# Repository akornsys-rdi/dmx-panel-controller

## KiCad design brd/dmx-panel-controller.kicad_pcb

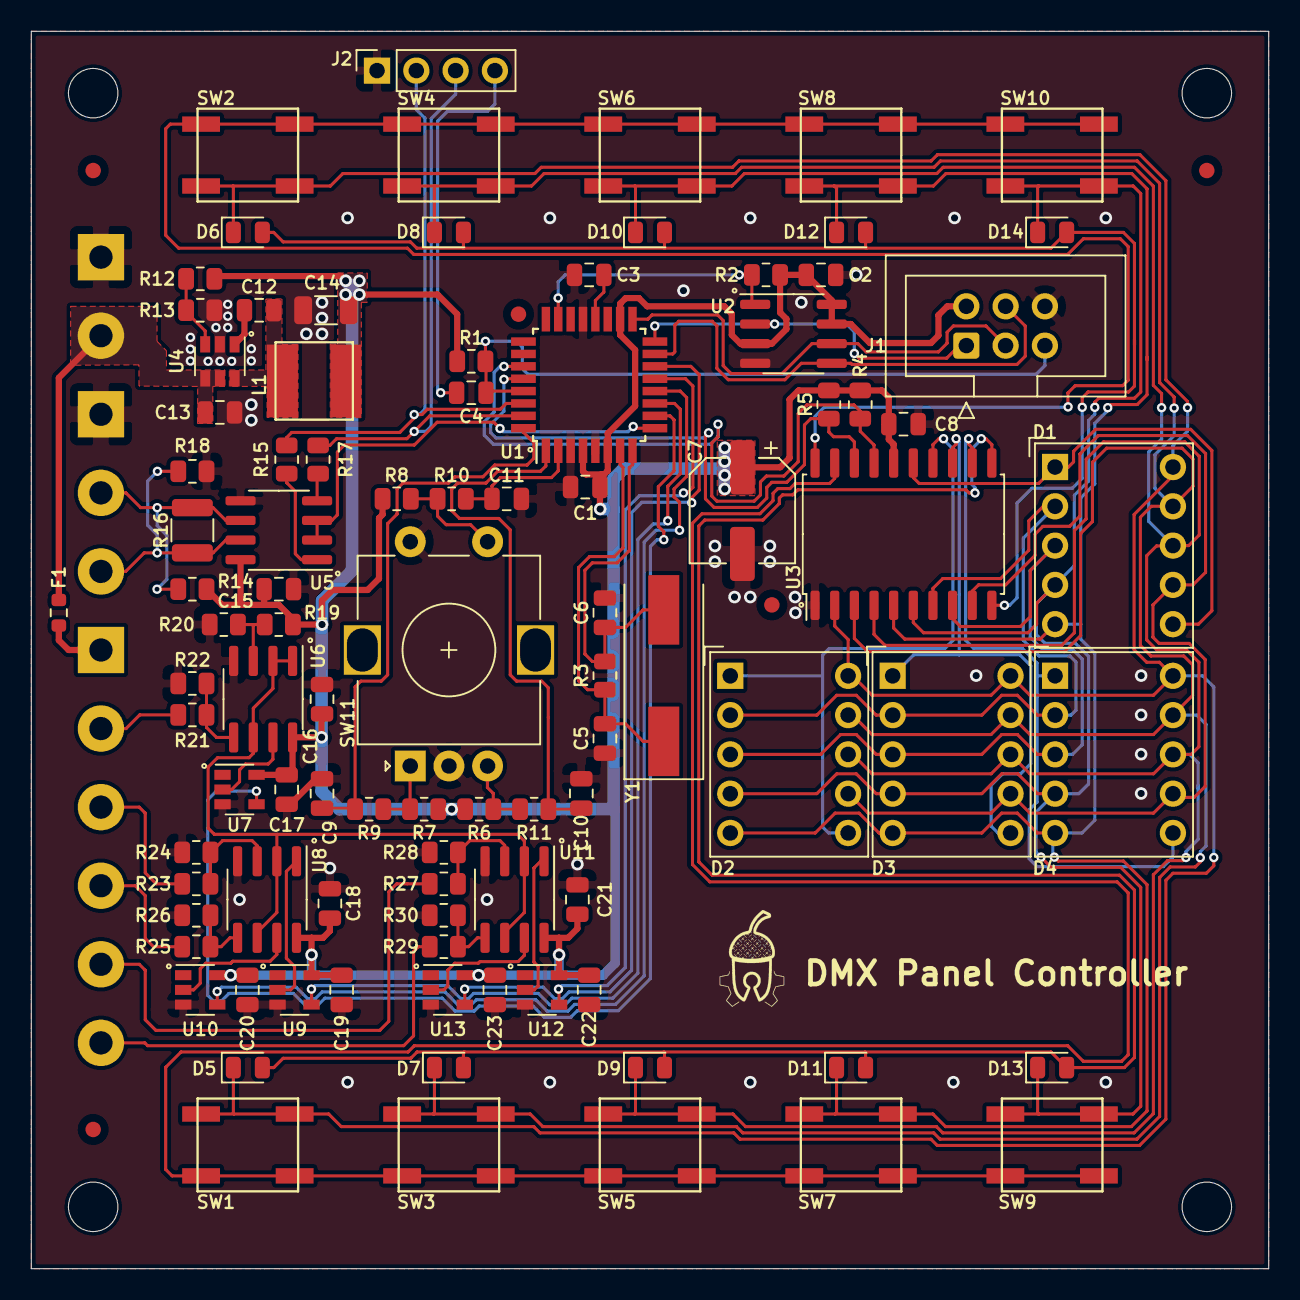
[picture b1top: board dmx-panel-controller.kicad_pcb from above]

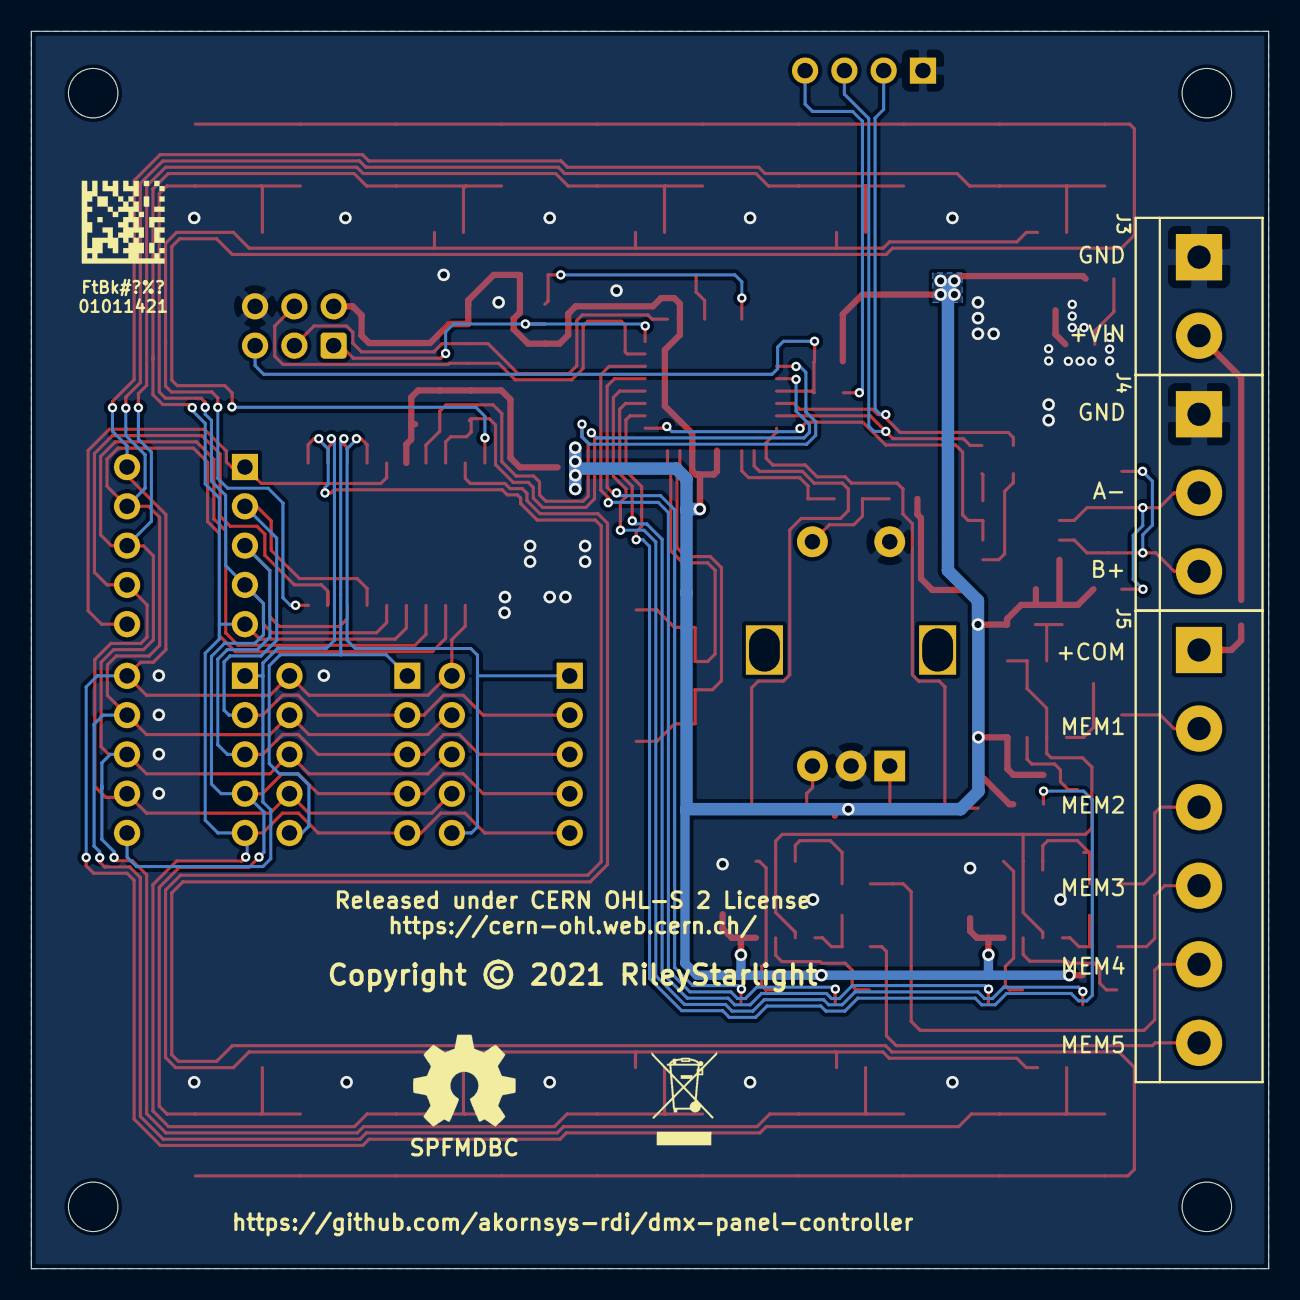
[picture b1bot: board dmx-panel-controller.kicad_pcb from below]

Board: 2 copper layers, 80.0 x 80.0 mm, 99 parts (3 on the bottom side), 69 nets.

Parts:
C1, C2, C3, C4, C8, C12, C15, C16, C17, C18, C19, C20, C21, C22, C23: 100nF; C_0805_2012Metric
C5, C6: 22pF; C_0805_2012Metric
C7: 220µF; CP_Elec_6.3x5.4
C9, C10, C11: 10nF; C_0805_2012Metric
C13: 4.7µF; C_0805_2012Metric
C14: 15µF; C_1206_3216Metric
D1, D2, D3, D4: SA39-12EWA; Sx39-1xxxxx
D5: RED; LED_0805_2012Metric
D6, D8, D10, D12, D13, D14: YELLOW; LED_0805_2012Metric
D7: GREEN; LED_0805_2012Metric
D9: BLUE; LED_0805_2012Metric
D11: WHITE; LED_0805_2012Metric
F1: 20mA; R_0603_1608Metric
J1: ISP; IDC-Header_2x03_P2.54mm_Vertical
J2: DEBUG; PinSocket_1x04_P2.54mm_Vertical
J3: POWER; TB006-508-02xx
J4: DMX; TB006-508-03xx
J5: INPUT; TB006-508-06xx
L1: 18µH; SRN5020
R1, R2, R4, R5, R6, R7, R8, R9, R10, R11, R19, R22, R24, R26, R28, R30: 10k; R_0805_2012Metric
R3: 1M; R_0805_2012Metric
R12: 88k7; R_0805_2012Metric
R13: 22k1; R_0805_2012Metric
R14, R18: 560R; R_0805_2012Metric
R15, R17: 1k; R_0805_2012Metric
R16: 120R; R_1210_3225Metric
R20: 4k7; R_0805_2012Metric
R21, R23, R25, R27, R29: 47k; R_0805_2012Metric
SW1, SW2, SW3, SW4, SW5, SW6, SW7, SW8, SW9, SW10: SW_Push; EVQ-Q2x0xW
SW11: Encoder; RotaryEncoder_Alps_EC11E-Switch_Vertical_H20mm
U1: ATmega328P-AU; TQFP-32_7x7mm_P0.8mm
U2: 25640; SOIC-8_3.9x4.9mm_P1.27mm
U3: TM1637; SOP-20_7.5x12.8mm_P1.27mm
U4: TPS560430; SOT-23-6
U5: SN65HVD82; SOIC-8_3.9x4.9mm_P1.27mm
U6, U8, U11: LM358; SOIC-8_3.9x4.9mm_P1.27mm
U7, U9, U10, U12, U13: 74LVC1G17; SOT-23-5
Y1: 16MHz; Crystal_SMD_HC49-SD

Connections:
+5V: C1.1, C2.1, C7.1, C8.1, C14.1, C15.1, C16.1, C17.1, C18.1, C19.1, C20.1, C21.1, C22.1, C23.1, J1.2, L1.2, R1.1, R2.1, R4.1, R5.1, R6.1, R7.1, R8.1, R12.1, R14.1, R19.1, U1.4, U1.6, U1.18, U2.3, U2.7, U2.8, U3.16, U5.8, U6.8, U7.5, U8.8, U9.5, U10.5, U11.8, U12.5, U13.5
+12V: C13.1, F1.1, J3.2, U4.4, U4.5
/DIR: U1.9, U5.2, U5.3
/ENC_A: C9.1, R9.2, U1.32
/ENC_B: C10.1, R11.2, U1.1
/HID/COL1: D1.1, D1.6, U3.15
/HID/COL2: D2.1, D2.6, U3.14
/HID/COL3: D3.1, D3.6, U3.13
/HID/COL4: D4.1, D4.6, U3.12
/HID/COL5: D5.2, D7.2, D9.2, D11.2, D13.2, U3.11
/HID/COL6: D6.2, D8.2, D10.2, D12.2, D14.2, U3.10
/HID/KEY1: SW1.1, SW3.1, SW5.1, SW7.1, SW9.1, U3.19
/HID/KEY2: SW2.1, SW4.1, SW6.1, SW8.1, SW10.1, U3.20
/HID/SEG_A: D1.10, D2.10, D3.10, D4.10, D5.1, D6.1, SW1.2, SW2.2, U3.2
/HID/SEG_B: D1.9, D2.9, D3.9, D4.9, D7.1, D8.1, SW3.2, SW4.2, U3.3
/HID/SEG_C: D1.8, D2.8, D3.8, D4.8, D9.1, D10.1, SW5.2, SW6.2, U3.4
/HID/SEG_D: D1.5, D2.5, D3.5, D4.5, D11.1, D12.1, SW7.2, SW8.2, U3.5
/HID/SEG_DP: D1.7, D2.7, D3.7, D4.7, U3.9
/HID/SEG_E: D1.4, D2.4, D3.4, D4.4, D13.1, D14.1, SW9.2, SW10.2, U3.6
/HID/SEG_F: D1.2, D2.2, D3.2, D4.2, U3.7
/HID/SEG_G: D1.3, D2.3, D3.3, D4.3, U3.8
/MEM1: U1.10, U7.4
/MEM2: U1.11, U9.4
/MEM3: U1.12, U10.4
/MEM4: U1.13, U12.4
/MEM5: U1.14, U13.4
/MISO: J1.1, U1.16, U2.2
/MOSI: J1.4, U1.15, U2.5
/RX: J2.2, R15.2, U1.30
/SCK: J1.3, U1.17, U2.6
/SCL: R5.2, U1.28, U3.18
/SDA: R4.2, U1.27, U3.17
/SW: C11.1, R10.1, U1.2
/TX: J2.3, R17.2, U1.31
/~RST: C4.2, J1.5, R1.2, U1.29
/~SS: R2.2, U1.23, U2.1
GND: C1.2, C2.2, C3.2, C5.2, C6.2, C7.2, C8.2, C9.2, C10.2, C11.2, C13.2, C14.2, C15.2, C16.2, C17.2, C18.2, C19.2, C20.2, C21.2, C22.2, C23.2, J1.6, J2.1, J3.1, J4.1, R13.2, R18.2, R20.2, R22.2, R24.2, R26.2, R28.2, R30.2, SW11.C, SW11.S2, U1.3, U1.5, U1.21, U2.4, U3.1, U4.2, U5.5, U6.4, U7.3, U8.4, U9.3, U10.3, U11.4, U12.3, U13.3
unnamed: C3.1, U1.20
unnamed: C4.1, J2.4
unnamed: C5.1, R3.1, U1.7, Y1.1
unnamed: C6.1, R3.2, U1.8, Y1.2
unnamed: C12.1, L1.1, U4.6
unnamed: C12.2, U4.1
unnamed: F1.2, J5.1
unnamed: J4.2, R14.2, R16.1, U5.6
unnamed: J4.3, R16.2, R18.1, U5.7
unnamed: J5.2, R21.2
unnamed: J5.3, R23.2
unnamed: J5.4, R25.2
unnamed: J5.5, R27.2
unnamed: J5.6, R29.2
unnamed: R7.2, R9.1, SW11.A
unnamed: R8.2, R10.2, SW11.S1
unnamed: R6.2, R11.1, SW11.B
unnamed: R12.2, R13.1, U4.3
unnamed: R15.1, U5.1
unnamed: R17.1, U5.4
unnamed: R19.2, R20.1, U6.3
unnamed: R21.1, R22.1, U6.5
unnamed: R23.1, R24.1, U8.3
unnamed: R25.1, R26.1, U8.5
unnamed: R27.1, R28.1, U11.3
unnamed: R29.1, R30.1, U11.5
unnamed: U6.7, U7.2
unnamed: U8.1, U9.2
unnamed: U8.7, U10.2
unnamed: U11.1, U12.2
unnamed: U6.1, U6.2, U6.6, U8.2, U8.6, U11.2, U11.6
unnamed: U11.7, U13.2

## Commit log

2021-04-13 feat: Upload the board with all the manufacturing files
2021-04-13 chore: Cleaned skeleton repository

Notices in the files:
brd/dmx-panel-controller.kicad_pcb:
Copyright © 2021 RileyStarlight, released under CERN OHL-S 2 License
https://cern-ohl.web.cern.ch
